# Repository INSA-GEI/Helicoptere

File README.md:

# Helicoptere
Modèle hélicoptère développé au GEI et utilisé en automatique 4éme année GEI

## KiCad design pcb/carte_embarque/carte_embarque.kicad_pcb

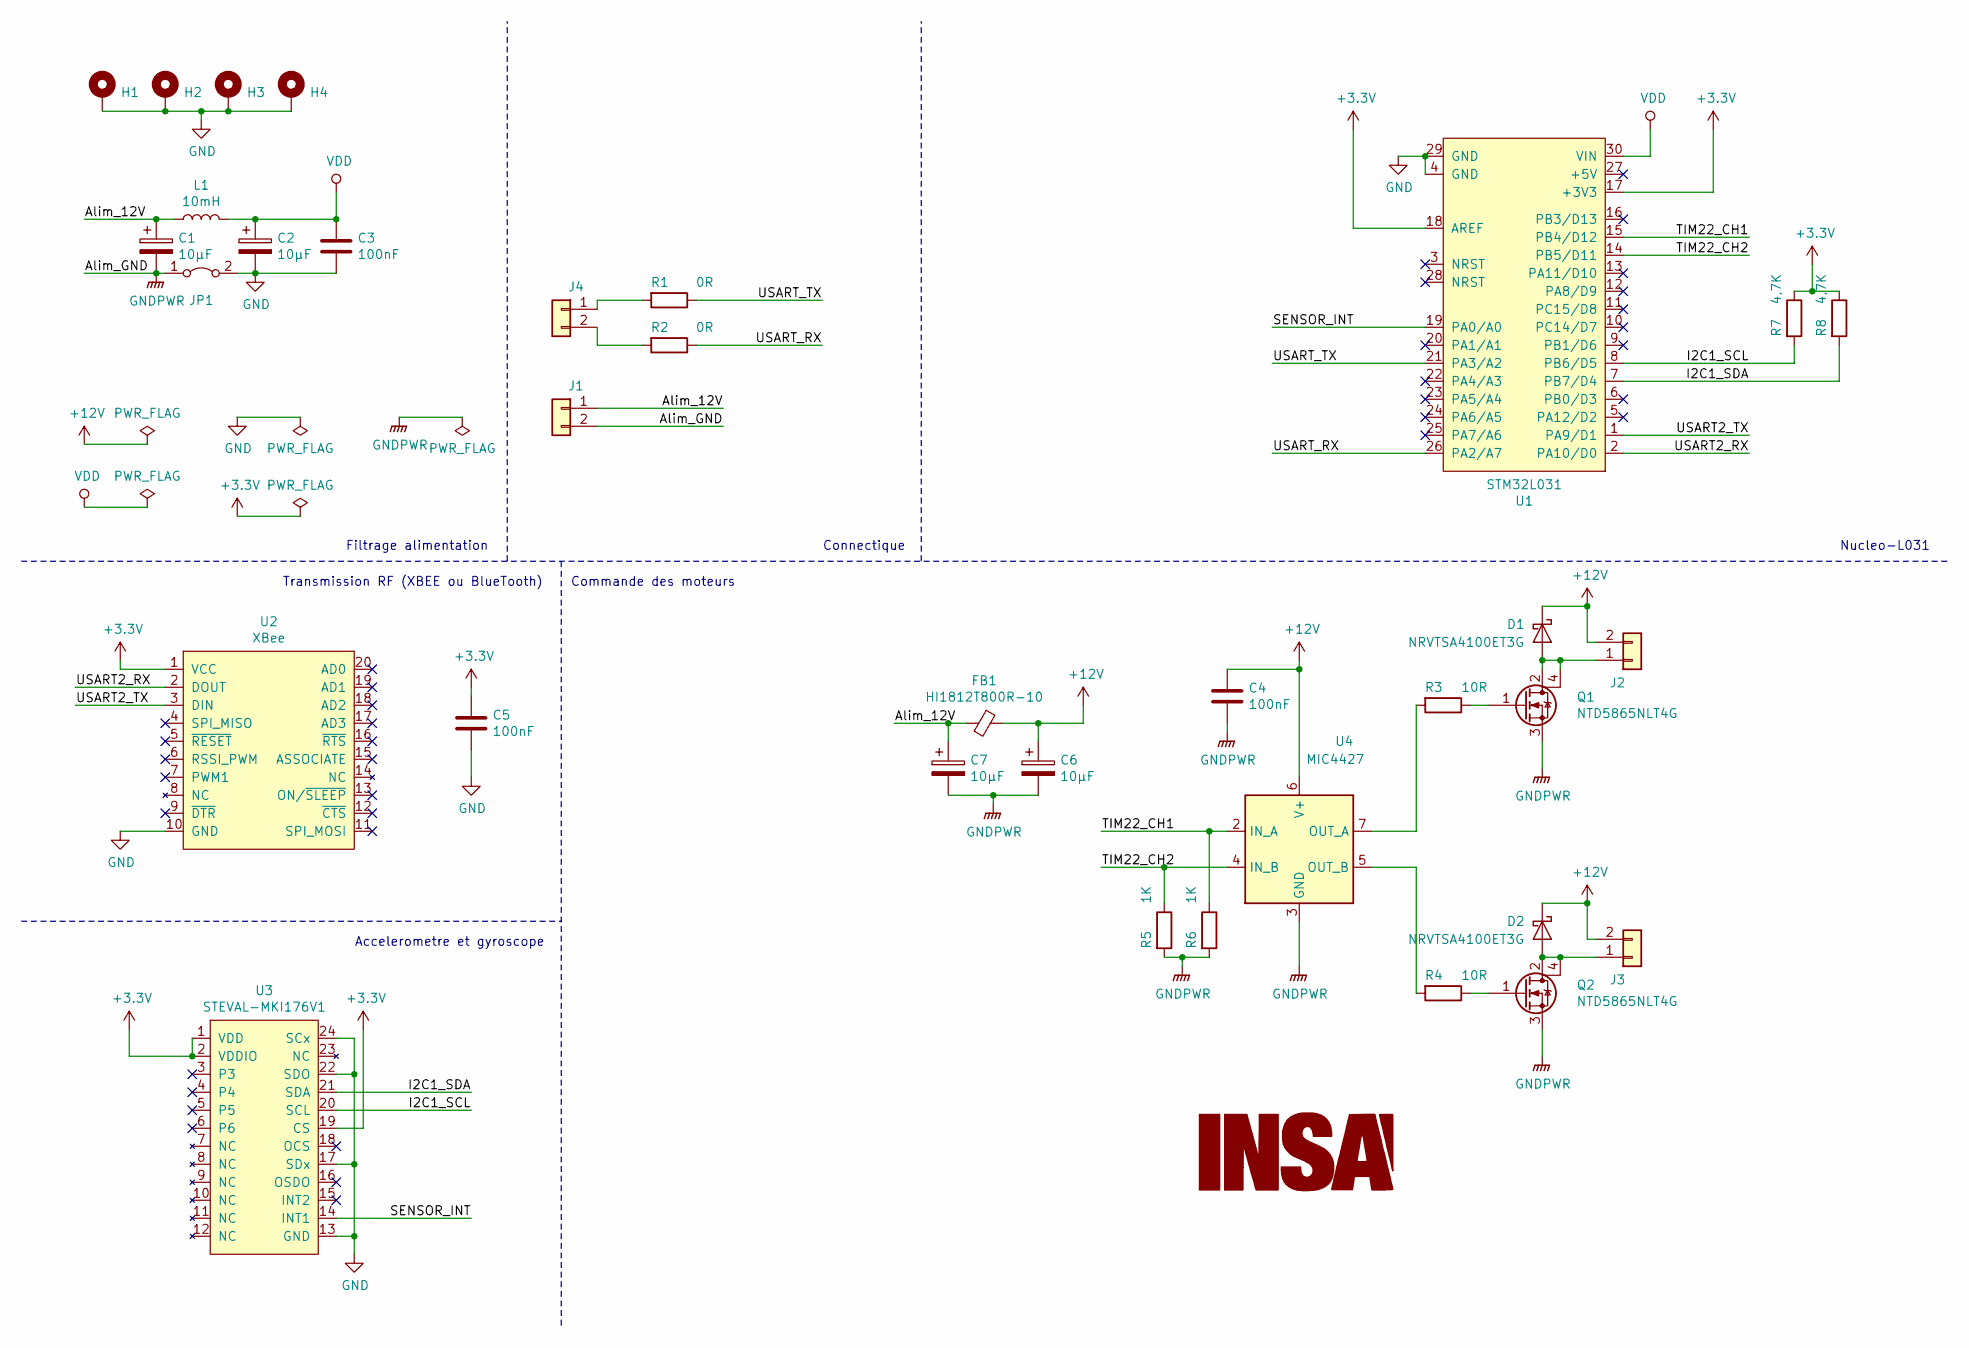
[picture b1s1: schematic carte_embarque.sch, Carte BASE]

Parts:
C1, C2, C6, C7: 10µF; CP_EIA-7343-31_Kemet-D
C3, C4, C5: 100nF; C_1206_3216Metric_Pad1.42x1.75mm_HandSolder
D1, D2: NRVTSA4100ET3G; D_SMA_Handsoldering
FB1: HI1812T800R-10; L_1812_4532Metric_Pad1.30x3.40mm_HandSolder
H1, H2, H3, H4: MountingHole_Pad; MountingHole_3.2mm_M3_ISO14580_Pad
J1, J2, J3: Conn_01x02; JST_VH_B2PS-VH_1x02_P3.96mm_Horizontal
J4: Conn_01x02; DF3A-2P-2DS
JP1: Jumper_2_Bridged; SolderJumper-2_P1.3mm_Bridged2Bar_RoundedPad1.0x1.5mm
L1: 10mH; L_Wuerth_WE-PD2-Typ-L
Q1, Q2: NTD5865NLT4G; TO-252-3_TabPin4
R1, R2: 0R; R_1206_3216Metric_Pad1.42x1.75mm_HandSolder
R3, R4: 10R; R_1206_3216Metric_Pad1.42x1.75mm_HandSolder
R5, R6: 1K; R_1206_3216Metric_Pad1.42x1.75mm_HandSolder
R7, R8: 4,7K; R_1206_3216Metric_Pad1.42x1.75mm_HandSolder
U1: STM32L031; STM32-Nucleo-32
U2: XBee; Xbee3
U3: STEVAL-MKI176V1; DIP-24_W15.24mm_Socket_LongPads
U4: MIC4427; SOIC-8_3.9x4.9mm_P1.27mm

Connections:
+3V3: C5.1, R7.1, R8.1, U1.17 (+3V3), U1.18 (AREF), U2.1 (VCC), U3.1 (VDD), U3.2 (VDDIO), U3.19 (CS)
+12V: C4.1, C6.1, D1.1 (K), D2.1 (K), FB1.1, J2.2, J3.2, U4.6 (V+)
/Alim_12V: C1.1, C7.1, FB1.2, J1.1, L1.1
/I2C1_SCL: R7.2, U1.8 (PB6/D5), U3.20 (SCL)
/I2C1_SDA: R8.2, U1.7 (PB7/D4), U3.21 (SDA)
/SENSOR_INT: U1.19 (PA0/A0), U3.14 (INT1)
/TIM22_CH1: R6.1, U1.15 (PB4/D12), U4.2 (IN_A)
/TIM22_CH2: R5.1, U1.14 (PB5/D11), U4.4 (IN_B)
/USART2_RX: U1.2 (PA10/D0), U2.2 (DOUT)
/USART2_TX: U1.1 (PA9/D1), U2.3 (DIN)
/USART_RX: R2.1, U1.26 (PA2/A7)
/USART_TX: R1.1, U1.21 (PA3/A2)
GND: C2.2, C3.2, C5.2, H1.1, H2.1, H3.1, H4.1, JP1.2 (B), U1.4 (GND), U1.29 (GND), U2.10 (GND), U3.13 (GND), U3.17 (SDx), U3.22 (SDO), U3.24 (SCx)
GNDPWR: C1.2, C4.2, C6.2, C7.2, J1.2, JP1.1 (A), Q1.3 (S), Q2.3 (S), R5.2, R6.2, U4.3 (GND)
unnamed: D1.2 (A), J2.1, Q1.2 (D), Q1.4 (D)
unnamed: D2.2 (A), J3.1, Q2.2 (D), Q2.4 (D)
unnamed: J4.1, R1.2
unnamed: J4.2, R2.2
unnamed: Q1.1 (G), R3.1
unnamed: Q2.1 (G), R4.1
unnamed: R3.2, U4.7 (OUT_A)
unnamed: R4.2, U4.5 (OUT_B)
VDD: C2.1, C3.1, L1.2, U1.30 (VIN)

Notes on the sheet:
Filtrage alimentation
Connectique
Nucleo-L031
Transmission RF (XBEE ou BlueTooth)
Commande des moteurs
Accelerometre et gyroscope

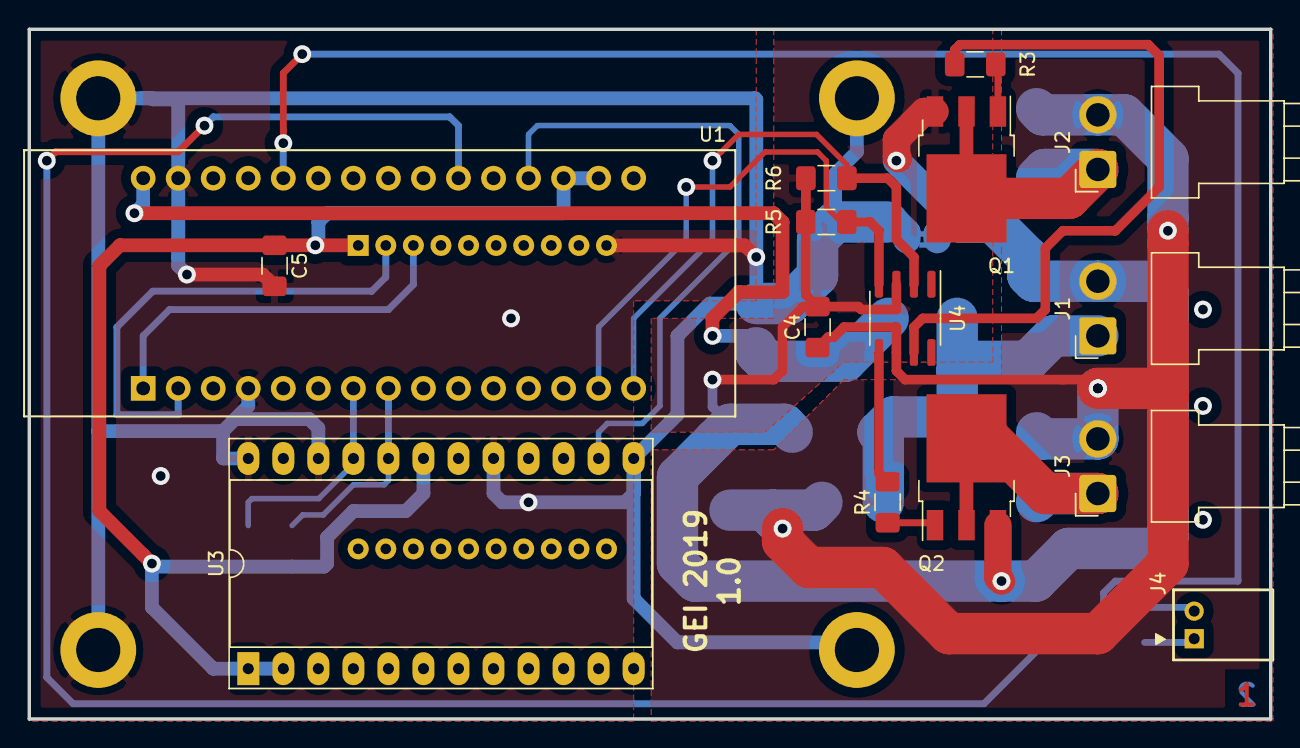
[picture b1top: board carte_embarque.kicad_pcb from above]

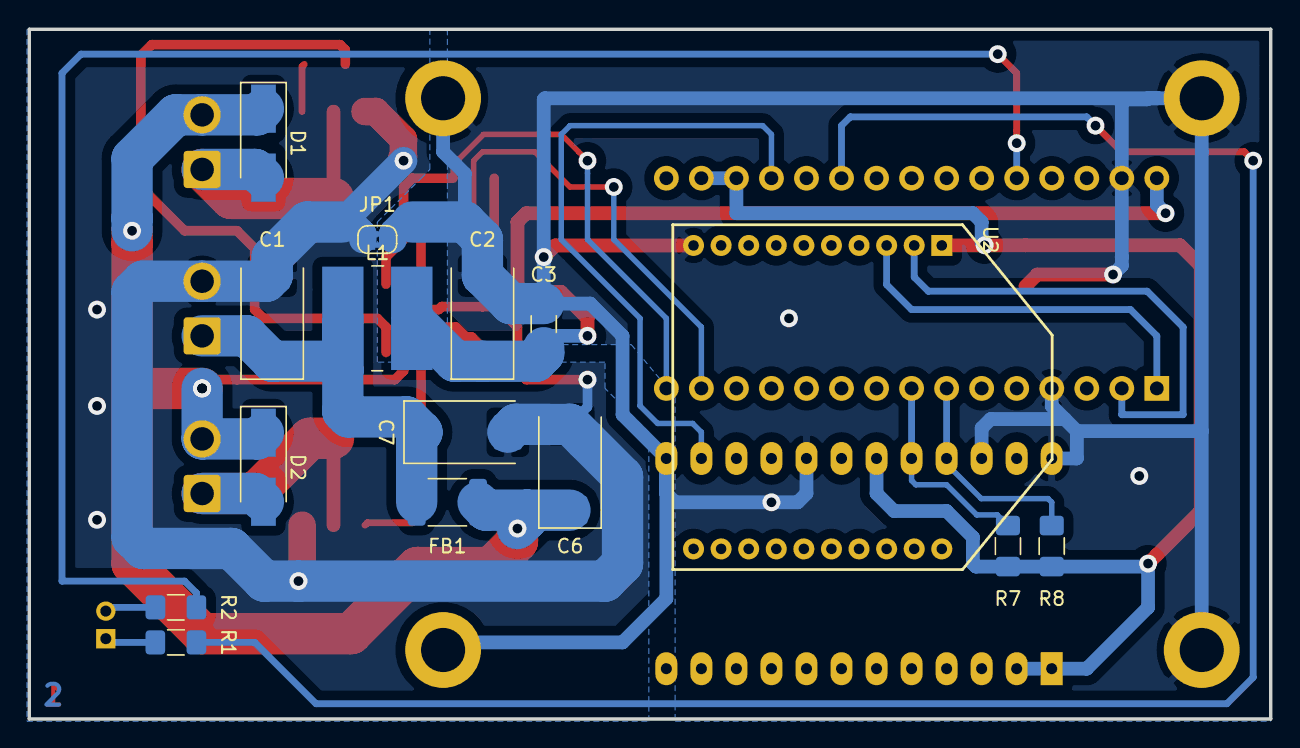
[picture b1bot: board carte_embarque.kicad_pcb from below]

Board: 2 copper layers, 90.0 x 50.0 mm, 34 parts (15 on the bottom side), 23 nets.

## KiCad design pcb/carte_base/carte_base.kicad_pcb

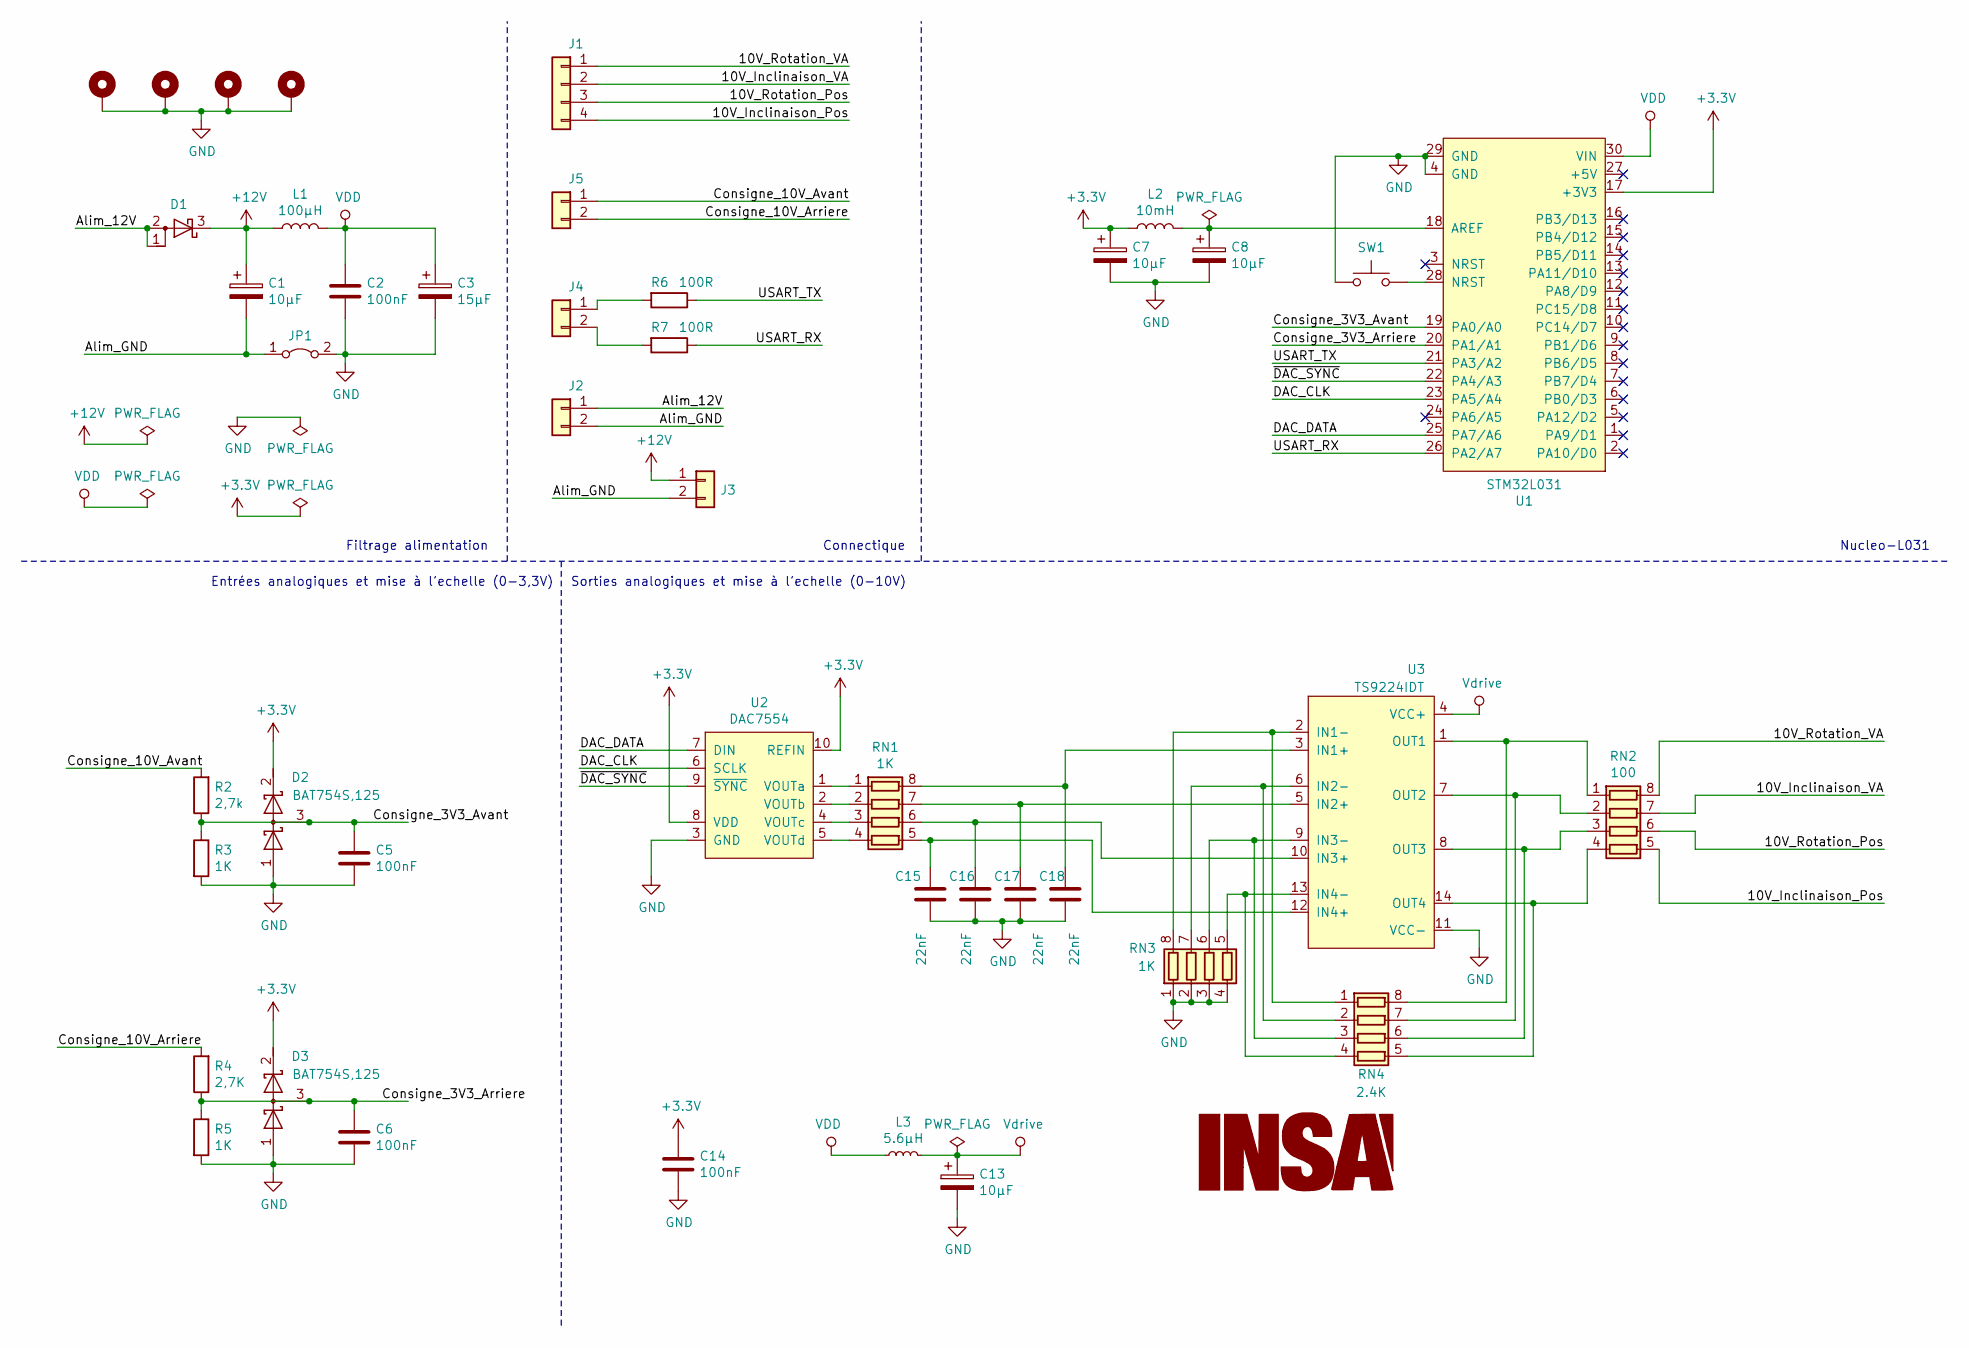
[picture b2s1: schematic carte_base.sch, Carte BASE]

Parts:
C1, C7, C8, C13: 10µF; CP_EIA-7343-31_Kemet-D
C2, C5, C6, C14: 100nF; C_1206_3216Metric_Pad1.42x1.75mm_HandSolder
C3: 15µF; CP_EIA-7343-31_Kemet-D
C15, C16, C17, C18: 22nF; C_1206_3216Metric_Pad1.42x1.75mm_HandSolder
D1: D_Schottky_AAK; TO-277A
D2, D3: BAT754S,125; SOT-23
H1, H2, H3, H4: MountingHole_Pad; MountingHole_3.2mm_M3_ISO14580_Pad
J1: Conn_01x04; DF3A-4P-2DS
J2, J3: Conn_01x02; JST_VH_B2PS-VH_1x02_P3.96mm_Horizontal
J4, J5: Conn_01x02; DF3A-2P-2DS
JP1: Jumper_2_Bridged; SolderJumper-2_P1.3mm_Bridged2Bar_RoundedPad1.0x1.5mm
L1: 100µH; L_Bourns-SRN6028
L2: 10mH; L_Wuerth_WE-PD2-Typ-L
L3: 5.6µH; L_1812_4532Metric_Pad1.30x3.40mm_HandSolder
R2: 2,7k; R_1206_3216Metric_Pad1.42x1.75mm_HandSolder
R3, R5: 1K; R_1206_3216Metric_Pad1.42x1.75mm_HandSolder
R4: 2,7K; R_1206_3216Metric_Pad1.42x1.75mm_HandSolder
R6, R7: 100R; R_1206_3216Metric_Pad1.42x1.75mm_HandSolder
RN1, RN3: 1K; R_Array_Convex_4x0603
RN2: 100; R_Array_Convex_4x0603
RN4: 2.4K; R_Array_Convex_4x0603
SW1: FSMRA3JH04; SW_Tactile_SPST_Angled_PTS645Vx58-2LFS
U1: STM32L031; STM32-Nucleo-32
U2: DAC7554; MSOP-10_3x3mm_P0.5mm
U3: TS9224IDT; SOIC-14_3.9x8.7mm_P1.27mm

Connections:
+3V3: C7.1, C14.1, D2.2 (K), D3.2 (K), L2.1, U1.17 (+3V3), U2.8 (VDD), U2.10 (REFIN)
+12V: C1.1, D1.3 (K), J3.1, L1.1
/10V_Inclinaison_Pos: J1.4, RN2.5 (R4.2)
/10V_Inclinaison_VA: J1.2, RN2.7 (R2.2)
/10V_Rotation_Pos: J1.3, RN2.6 (R3.2)
/10V_Rotation_VA: J1.1, RN2.8 (R1.2)
/Alim_12V: D1.1 (A), D1.2 (A), J2.1
/Alim_GND: C1.2, J2.2, J3.2, JP1.1 (A)
/Consigne_3V3_Arriere: C6.1, D3.3 (common), R4.1, R5.1, U1.20 (PA1/A1)
/Consigne_3V3_Avant: C5.1, D2.3 (common), R2.1, R3.1, U1.19 (PA0/A0)
/Consigne_10V_Arriere: J5.2, R4.2
/Consigne_10V_Avant: J5.1, R2.2
/DAC_CLK: U1.23 (PA5/A4), U2.6 (SCLK)
/DAC_DATA: U1.25 (PA7/A6), U2.7 (DIN)
/USART_RX: R7.1, U1.26 (PA2/A7)
/USART_TX: R6.1, U1.21 (PA3/A2)
/~DAC_SYNC: U1.22 (PA4/A3), U2.9 (~SYNC)
GND: C2.2, C3.2, C5.2, C6.2, C7.2, C8.2, C13.2, C14.2, C15.2, C16.2, C17.2, C18.2, D2.1 (A), D3.1 (A), H1.1, H2.1, H3.1, H4.1, JP1.2 (B), R3.2, R5.2, RN3.1 (R1.1), RN3.2 (R2.1), RN3.3 (R3.1), RN3.4 (R4.1), SW1.1, U1.4 (GND), U1.29 (GND), U2.3 (GND), U3.11 (VCC-)
unnamed: C8.1, L2.2, U1.18 (AREF)
unnamed: C15.1, RN1.5 (R4.2), U3.12 (IN4+)
unnamed: C16.1, RN1.6 (R3.2), U3.10 (IN3+)
unnamed: C17.1, RN1.7 (R2.2), U3.5 (IN2+)
unnamed: C18.1, RN1.8 (R1.2), U3.3 (IN1+)
unnamed: J4.1, R6.2
unnamed: J4.2, R7.2
unnamed: RN1.1 (R1.1), U2.1 (VOUTa)
unnamed: RN1.2 (R2.1), U2.2 (VOUTb)
unnamed: RN1.3 (R3.1), U2.4 (VOUTc)
unnamed: RN1.4 (R4.1), U2.5 (VOUTd)
unnamed: RN2.1 (R1.1), RN4.8 (R1.2), U3.1 (OUT1)
unnamed: RN2.2 (R2.1), RN4.7 (R2.2), U3.7 (OUT2)
unnamed: RN2.3 (R3.1), RN4.6 (R3.2), U3.8 (OUT3)
unnamed: RN2.4 (R4.1), RN4.5 (R4.2), U3.14 (OUT4)
unnamed: RN3.5 (R4.2), RN4.4 (R4.1), U3.13 (IN4-)
unnamed: RN3.6 (R3.2), RN4.3 (R3.1), U3.9 (IN3-)
unnamed: RN3.7 (R2.2), RN4.2 (R2.1), U3.6 (IN2-)
unnamed: RN3.8 (R1.2), RN4.1 (R1.1), U3.2 (IN1-)
unnamed: SW1.2, U1.28 (NRST)
VDD: C2.1, C3.1, L1.2, L3.2, U1.30 (VIN)
Vdrive: C13.1, L3.1, U3.4 (VCC+)

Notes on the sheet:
Filtrage alimentation
Connectique
Nucleo-L031
Entrées analogiques et mise à l'echelle (0-3,3V)
Sorties analogiques et mise à l'echelle (0-10V)

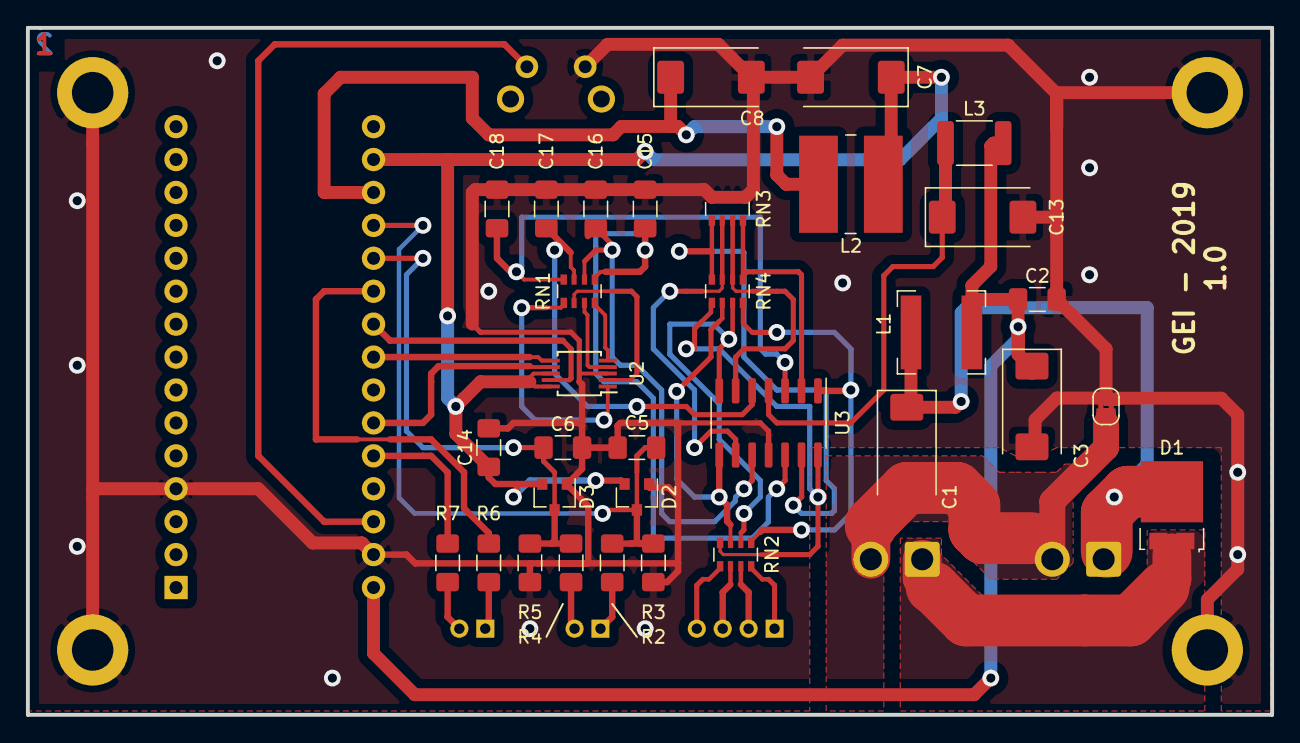
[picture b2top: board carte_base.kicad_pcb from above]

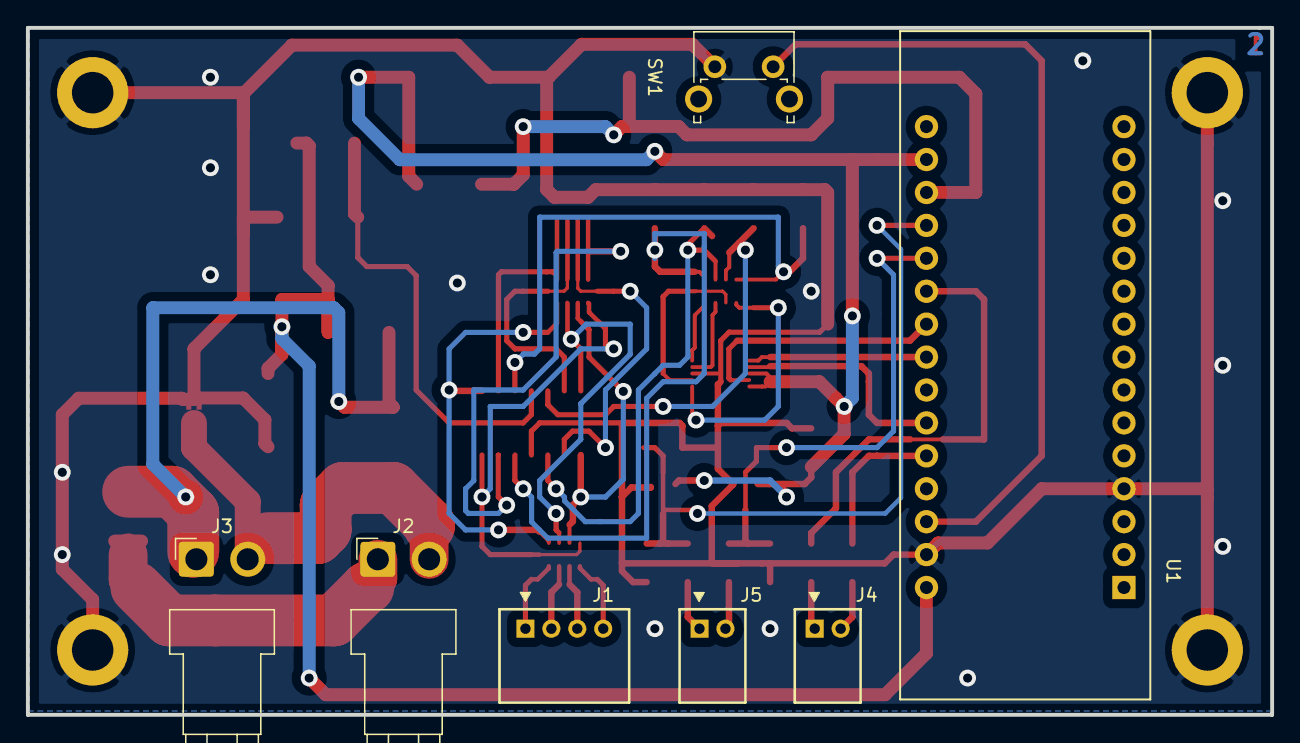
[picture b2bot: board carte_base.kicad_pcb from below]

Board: 2 copper layers, 96.0 x 53.0 mm, 43 parts (7 on the bottom side), 40 nets.

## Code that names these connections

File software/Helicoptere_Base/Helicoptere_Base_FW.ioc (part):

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Mcu.Name=STM32L031K(4-6)Tx
Mcu.Package=LQFP32
Mcu.UserName=STM32L031K6Tx
PA0-CK_IN.Mode=IN0
PA0-CK_IN.Signal=ADC_IN0
PA1.Mode=IN1
PA1.Signal=ADC_IN1
PA13.GPIOParameters=GPIO_Label
PA13.GPIO_Label=TMS
PA13.Mode=Serial_Wire
PA13.Signal=SYS_SWDIO
PA14.GPIOParameters=GPIO_Label
PA14.GPIO_Label=TCK
PA14.Mode=Serial_Wire
PA14.Signal=SYS_SWCLK
PA2.GPIOParameters=GPIO_Label
PA2.GPIO_Label=USART_TX
PA2.Mode=Asynchronous
PA2.Signal=USART2_TX
PA3.GPIOParameters=GPIO_Label
PA3.GPIO_Label=USART_RX
PA3.Mode=Asynchronous
PA3.Signal=USART2_RX
PA4.GPIOParameters=GPIO_Speed,PinState,GPIO_Label
PA4.GPIO_Label=DAC_SYNC
PA4.GPIO_Speed=GPIO_SPEED_FREQ_MEDIUM
PA4.PinState=GPIO_PIN_SET
PA4.Signal=GPIO_Output
PA5.GPIOParameters=GPIO_Label
PA5.GPIO_Label=DAC_CLK
PA5.Mode=TX_Only_Simplex_Unidirect_Master
PA5.Signal=SPI1_SCK
PA7.GPIOParameters=GPIO_Label
PA7.GPIO_Label=DAC_DATA
PA7.Mode=TX_Only_Simplex_Unidirect_Master
PA7.Signal=SPI1_MOSI
PB3.GPIOParameters=GPIO_Speed,GPIO_Label
PB3.GPIO_Label=LED
PB3.GPIO_Speed=GPIO_SPEED_FREQ_VERY_HIGH
PB3.Signal=S_TIM2_CH2
PC14-OSC32_IN.Signal=RCC_OSC32_IN
PC15-OSC32_OUT.Signal=RCC_OSC32_OUT
RCC.HSE_VALUE=8000000
RCC.SYSCLKFreq_VALUE=32000000
RCC.SYSCLKSource=RCC_SYSCLKSOURCE_PLLCLK
board=NUCLEO-L031K6
boardIOC=true

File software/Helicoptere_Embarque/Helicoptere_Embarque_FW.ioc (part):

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Mcu.Name=STM32L432K(B-C)Ux
Mcu.Package=UFQFPN32
Mcu.UserName=STM32L432KCUx
PA0.GPIOParameters=GPIO_Label
PA0.GPIO_Label=MCO [High speed clock in]
PA0.Mode=HSE-External-Clock-Source-for-LittleOrca
PA0.Signal=RCC_CK_IN
PA1.GPIOParameters=GPIO_Label
PA1.GPIO_Label=SENSOR_INT
PA1.Signal=GPXTI1
PA10.Mode=Asynchronous
PA10.Signal=USART1_RX
PA11.Signal=S_TIM1_CH4
PA13\ (JTMS-SWDIO).GPIOParameters=GPIO_Label
PA13\ (JTMS-SWDIO).GPIO_Label=SWDIO
PA13\ (JTMS-SWDIO).Signal=SYS_JTMS-SWDIO
PA14\ (JTCK-SWCLK).GPIOParameters=GPIO_Label
PA14\ (JTCK-SWCLK).GPIO_Label=SWCLK
PA14\ (JTCK-SWCLK).Signal=SYS_JTCK-SWCLK
PA2.Mode=Asynchronous
PA2.Signal=USART2_TX
PA3.Mode=Asynchronous
PA3.Signal=USART2_RX
PA8.Signal=S_TIM1_CH1
PA9.Mode=Asynchronous
PA9.Signal=USART1_TX
PB3\ (JTDO-TRACESWO).Signal=S_TIM2_CH2
PB6.Mode=I2C
PB6.Signal=I2C1_SCL
PB7.Mode=I2C
PB7.Signal=I2C1_SDA
PC14-OSC32_IN\ (PC14).Signal=RCC_OSC32_IN
PC15-OSC32_OUT\ (PC15).Signal=RCC_OSC32_OUT
RCC.HSE_VALUE=8000000
RCC.SYSCLKFreq_VALUE=80000000
RCC.SYSCLKSource=RCC_SYSCLKSOURCE_PLLCLK
board=NUCLEO-L432KC
boardIOC=true

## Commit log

2019-09-24 Etat initial
2019-09-27 Etape intermediaire
2019-10-01 Carte base finie
2019-10-03 Carte embarquée terminée
2019-10-03 Correction sur carte base
2019-10-11 petites evolutions sur PCB
2019-11-13 creation du projet logiciel Helicoptere_embarque
2019-11-15 ajout des drivers usart (XBEE et BASE_COM) et de l'accelero_gyro. Les usarts semblent bien marcher, mais l'accelero ne marche pas encore (pb d'I2C)
2019-11-18 Reglage du gyrosocpe et de l'accelerometre, ajout de routine AHRS
2019-11-19 AHRS raisonnablement stable et fonctionnel F=500Hz mais probleme autour de +/-180°
2019-11-21 Creation du projet helicoptere_base
2019-11-29 Periph soft de base OK
2019-12-09 Multiple evolutions et corrections
2019-12-10 Changement de loi AHRS
2020-06-23 Ajout de la doc, premier draft
